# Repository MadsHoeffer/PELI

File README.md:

This repository shows the work done in the course Project In Embedded Linux.
The projects consists of two components:

1. Magnetic door sensor.
A magnetic door sensor that can be used to remotely monitor if a door is open or not. 3D files for the casing, KiCad design and code is available.

2. ChatGPT dictaphone.
A device that can be used to ask ChatGPT questions remotely. 3D files for the casing, KiCad design, code for the ESP32 and audio receiver (Raspberry Pi) is available.
Requires a OpenAI API key

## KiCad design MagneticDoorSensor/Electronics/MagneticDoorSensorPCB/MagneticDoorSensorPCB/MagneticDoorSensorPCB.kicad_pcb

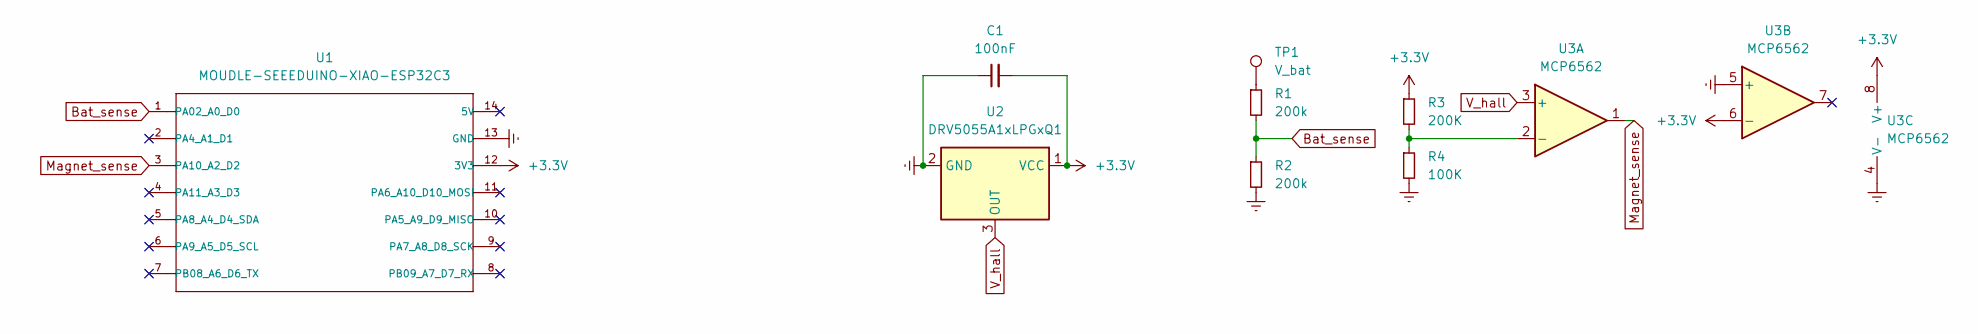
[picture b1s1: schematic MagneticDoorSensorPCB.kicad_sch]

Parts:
C1: 100nF; C_0805_2012Metric_Pad1.18x1.45mm_HandSolder
R1, R2: 200k; R_0805_2012Metric_Pad1.20x1.40mm_HandSolder
R3: 200K; R_0805_2012Metric_Pad1.20x1.40mm_HandSolder
R4: 100K; R_0805_2012Metric_Pad1.20x1.40mm_HandSolder
TP1: V_bat; TestPoint_Pad_2.0x2.0mm
U1: MOUDLE-SEEEDUINO-XIAO-ESP32C3; MOUDLE14P-SMD-2.54-21X17.8MM_THT
U2: DRV5055A1xLPGxQ1; TO-92_Inline
U3: MCP6562; DIP-8_W7.62mm

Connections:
+3.3V: C1.2, R3.1, U1.12 (3V3), U2.1 (VCC), U3.6 (-), U3.8 (V+)
Bat_sense: R1.2, R2.1, U1.1 (PA02_A0_D0)
Earth: C1.1, R2.2, R4.2, U1.13 (GND), U2.2 (GND), U3.4 (V-), U3.5 (+)
Magnet_sense: U1.3 (PA10_A2_D2), U3.1
unnamed: R1.1, TP1.1
unnamed: R3.2, R4.1, U3.2 (-)
V_hall: U2.3 (OUT), U3.3 (+)

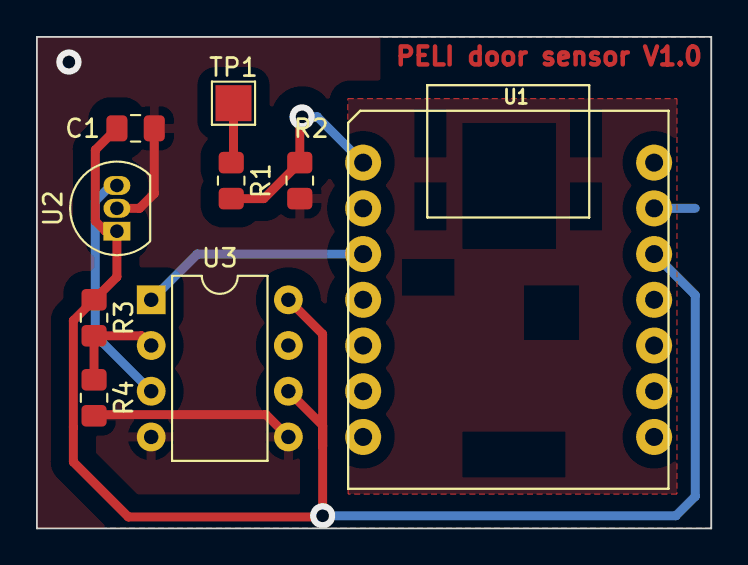
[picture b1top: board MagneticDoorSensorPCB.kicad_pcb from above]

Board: 2 copper layers, 37.5 x 27.3 mm, 9 parts (0 on the bottom side), 7 nets.

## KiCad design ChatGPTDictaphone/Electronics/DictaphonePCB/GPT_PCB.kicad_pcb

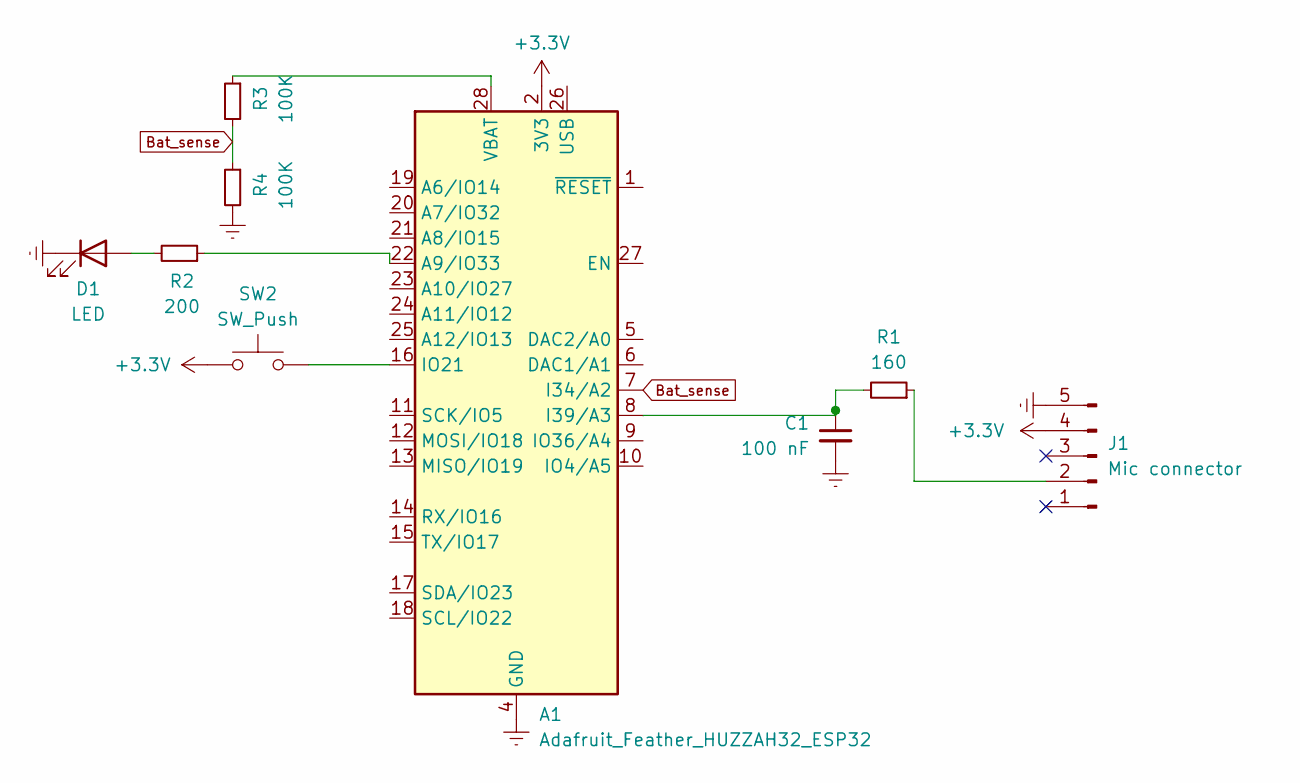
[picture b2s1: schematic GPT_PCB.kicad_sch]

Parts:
A1: Adafruit_Feather_HUZZAH32_ESP32; Adafruit_Feather
C1: 100 nF; C_0805_2012Metric_Pad1.18x1.45mm_HandSolder
D1: LED; LED_D4.0mm
J1: Mic connector; PinHeader_1x05_P2.54mm_Vertical
R1: 160; R_0805_2012Metric_Pad1.20x1.40mm_HandSolder
R2: 200; R_0805_2012Metric_Pad1.20x1.40mm_HandSolder
R3, R4: 100K; R_0805_2012Metric_Pad1.20x1.40mm_HandSolder
SW2: SW_Push; SW_PUSH_6mm_H5mm

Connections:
+3.3V: A1.2 (3V3), J1.4, SW2.1
Bat_sense: A1.7 (I34/A2), R3.2, R4.1
Earth: A1.4 (GND), C1.2, D1.1 (K), J1.5, R4.2
unnamed: A1.22 (A9/IO33), R2.1
unnamed: A1.8 (I39/A3), C1.1, R1.2
unnamed: A1.16 (IO21), SW2.2
unnamed: A1.28 (VBAT), R3.1
unnamed: D1.2 (A), R2.2
unnamed: J1.2, R1.1

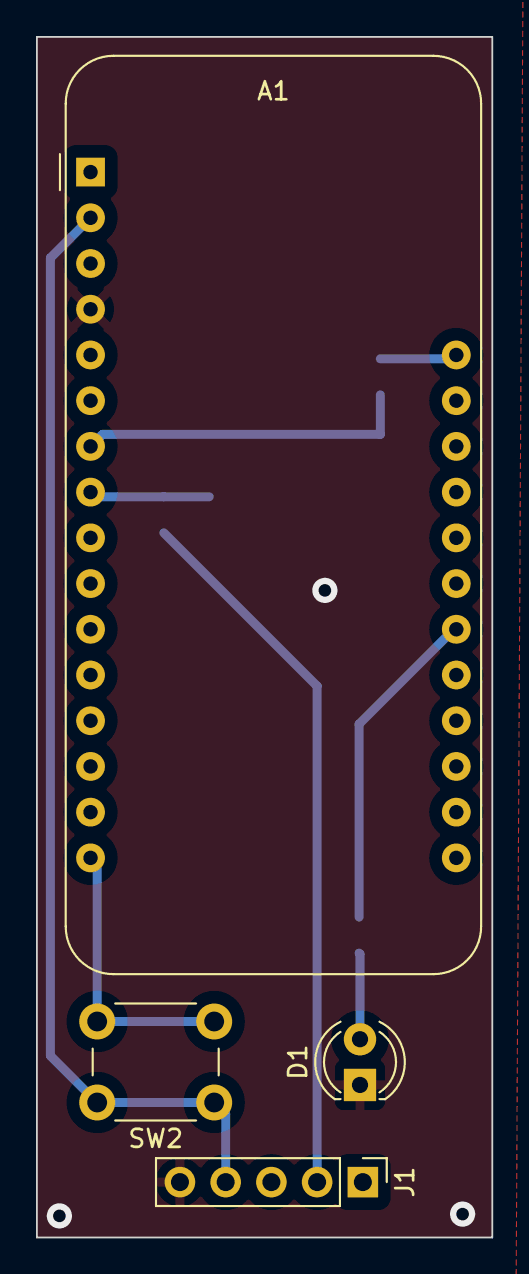
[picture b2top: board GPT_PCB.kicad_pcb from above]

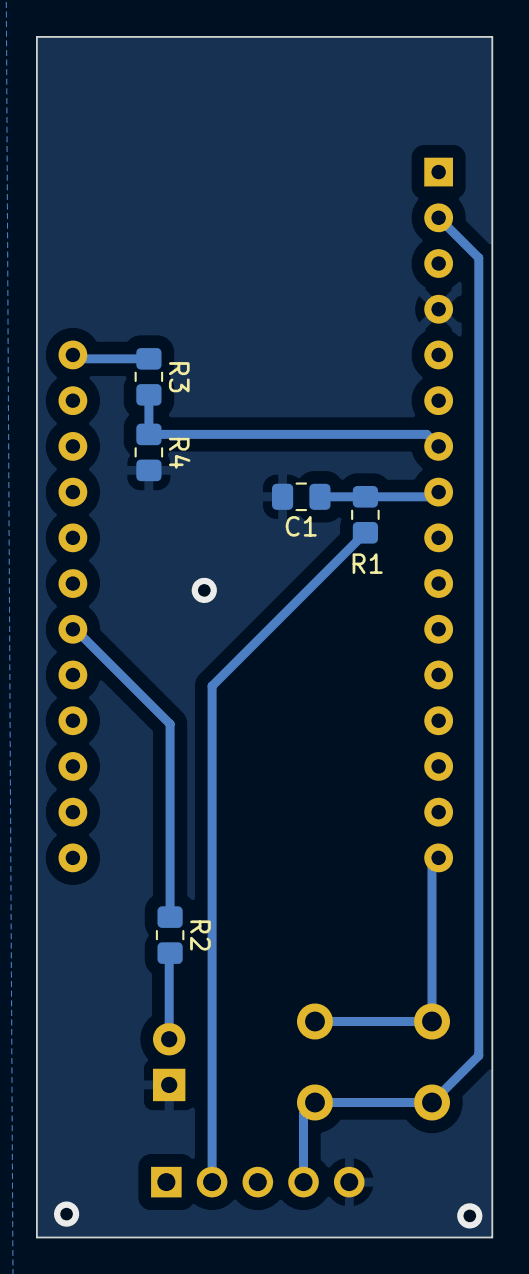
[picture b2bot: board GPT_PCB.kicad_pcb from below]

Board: 2 copper layers, 25.3 x 66.7 mm, 9 parts (5 on the bottom side), 9 nets.

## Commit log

2024-01-13 Structure + PCBs + 3D models + ESP audio + Audio receiver
2024-01-13 Fusion model of dictaphone case
2024-01-14 magnetic door sensor code + 3d models
2024-01-14 Small change to Doorsensor code
2024-01-15 Slight changes to code
